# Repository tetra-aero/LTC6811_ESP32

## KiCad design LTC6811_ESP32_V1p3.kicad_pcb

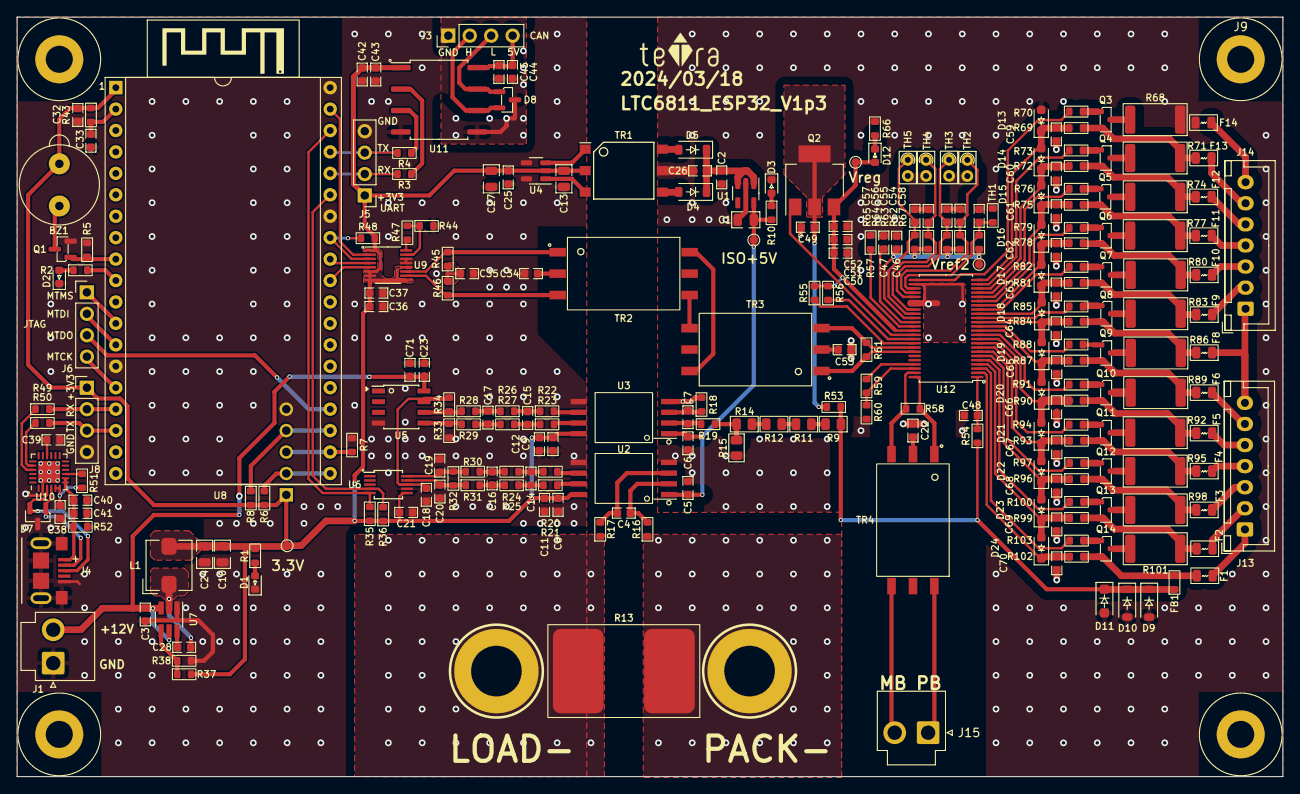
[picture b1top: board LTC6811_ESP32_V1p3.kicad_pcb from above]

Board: 2 copper layers, 150.0 x 90.0 mm, 262 parts (1 on the bottom side), 184 nets.

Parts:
BAT1: BAT-; Battery_6mm×10mm_Cell_half_2
BAT-1: BAT-; Battery_6mm×10mm_Cell_half_2
BZ1: AI-1027-TWT-5V; Beeper_AI-1027-TWT-5V
C1, C10, C13, C24, C27: 10uF/16V; C_0805_2012Metric
C2, C5, C6, C8, C9, C18, C19, C20, C21, C23, C25, C28, C32, C33, C37, C40, C43, C45, C48, C49, C54, C55, C56, C57, C58, C59, C60, C61, C62, C63, C64, C65, C66, C67, C68, C69, C70: 100nF/100V; C_0603_1608Metric
C3, C11, C12, C38, C41: 2.2uF/25V; C_0603_1608Metric
C4, C7: 330pF/100V; C_0603_1608Metric
C14, C15: 2.2nF/16V; C_0603_1608Metric
C16, C17: 220pF/50V; C_0603_1608Metric
C22, C53: 100pF/100V; C_0603_1608Metric
C26, C39: 4.7uF/16V; C_0603_1608Metric
C34, C35: 10nF/100V; C_0603_1608Metric
C36, C42, C44, C46, C47, C50, C51, C52, C71: 1uF/25V; C_0603_1608Metric
D1, D2, D3, D12: LED Red; LED_0603_1608Metric
D4, D5: MBR0520; D_SOD-123
D7, D8: ESD24VS2U; SOT-23
D9, D10: 1N4148W; D_SOD-123
D11: BZT52H-C62; D_SOD-123F
D13, D14, D15, D16, D17, D18, D19, D20, D21, D22, D23, D24: PDZ7.5B; D_SOD-323_HandSoldering
F1, F2, F3, F4, F5, F6, F8, F9, F10, F11, F12, F13, F14: MPZ2012S102ATD25; Fuse_0805_2012Metric
FB1: BLM18PG330SN1D; R_0603_1608Metric
J1, J15: PB MB; JST_VH_B2P-VH-B_1x02_P3.96mm_Vertical
J2: OLED /NC; PinHeader_1x05_P2.54mm_Vertical
J3: CAN /NC; PinHeader_1x04_P2.54mm_Vertical
J4: USB; Micro_USB_B-2013499-1
J5: UART /NC; PinHeader_1x04_P2.54mm_Vertical
J6: JTAG /NC; PinHeader_1x04_P2.54mm_Vertical
J8: SERIAL /NC; PinHeader_1x04_P2.54mm_Vertical
J9, J10, J11, J12: Hole /NC; MountingHole_3.2mm_M3_ISO7380_Pad
J13, J14: B7B-XH-A; JST_XH_B7B-XH-A_1x07_P2.50mm_Vertical_BAT_6S
L1: 3.3uH; L_Bourns_SRP5030T
LOGO1: teTra /NC; teTra-LOGO
Q1: BSS138; SOT-23
Q2: NSV1C201MZ4; SOT-223
Q3, Q4, Q5, Q6, Q7, Q8, Q9, Q10, Q11, Q12, Q13, Q14: TSM2323; SOT-23
R1, R2, R10: 470R; R_0603_1608Metric
R3, R4, R55, R57: 0; R_0603_1608Metric
R5: 1.5K; R_0603_1608Metric
R6, R7, R8, R35, R36: 4.7K; R_0603_1608Metric
R9, R11, R12, R14: 470KΩ ±0.1% 250mW; R_0805_2012Metric
R13: 0.1MR 1% 15W; R_PSR500HTQFB0L10_Metric_Pad5.2x8.75mm_HandSolder
R15: 1KΩ ±0.1% 250mW; R_0805_2012Metric
R16, R17, R18, R24, R25, R26, R27, R32: 1K; R_0603_1608Metric
R19: 10R; R_0603_1608Metric
R20, R21, R22, R23, R53, R54, R61, R69, R72, R75, R78, R81, R84, R87, R90, R93, R96, R99, R102: 100R; R_0603_1608Metric
R28, R29: 5.6K; R_0603_1608Metric
R30, R31, R70, R73, R76, R79, R82, R85, R88, R91, R94, R97, R100, R103: 3.3K; R_0603_1608Metric
R33, R34: 33K; R_0603_1608Metric
R37, R58, R62, R63, R64, R65, R67: 100K; R_0603_1608Metric
R38: 22.1K; R_0603_1608Metric
R43, R51, R52: 10K; R_0603_1608Metric
R44, R60: 806R; R_0603_1608Metric
R45, R46: 51R; R_0603_1608Metric
R47, R59, R66: 1.2K; R_0603_1608Metric
R48: 2K; R_0603_1608Metric
R49, R50: 240R; R_0603_1608Metric
R56: 1M; R_0603_1608Metric
R68, R71, R74, R77, R80, R83, R86, R89, R92, R95, R98, R101: 36R 1W 2512; R_2512_6332Metric
TH1: 100K NTC; R_0603_1608Metric
TH2, TH3, TH4, TH5: 100K NTC; R_Axial_DIN0204_L3.6mm_D1.6mm_P1.90mm_Vertical
TP1, TP2, TP3, TP4: TestPoint; TestPoint_Pad_D1.0mm
TR1: Transformer; WURTH-760390015
TR2, TR3, TR4: HM2108NL
U1: TPS76350; SOT-23-5
U2: AMC1301 or AMC1302; SSO-8_6.8x5.9mm_P1.27mm_Clearance8mm
U3: AMC1301; SSO-8_6.8x5.9mm_P1.27mm_Clearance8mm
U4: SN6501DBV; SOT-23-5
U5: OPA2197IDR; SOIC-8_3.9x4.9mm_Pitch1.27mm
U6: ISL28022; MSOP-10_3x3mm_P0.5mm
U7: LMR51420XDDCR; SOT-23-6_Handsoldering
U8: ESP32-DevKitC V4; ESP32-DevKitc V4_DIP-38_27.9mm×48.2mm
U9: LTC6820; MSOP-16_3x4mm_P0.5mm
U10: CP2104; HVQFN-24-1EP_4x4mm_P0.5mm_EP2.6x2.6mm
U11: ISO1050DUBR; SOP-8_6.62x9.15mm_P2.54mm
U12: LTC6811HG-1; TSSOP-48_6.1x12.5mm_P0.5mm

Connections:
+3V3: BZ1.1 (-), C8.1, C9.1, C10.1, C11.1, C12.1, C13.1, C21.2, C24.1, C25.1, C27.1, C32.2, C36.2, C37.1, C42.1, C43.1, J2.1, J5.1, J8.1, L1.2, R1.2, R6.2, R8.2, R35.1, R36.1, R37.2, R43.1, R48.1, TP2.1, TR1.2, U2.8 (VDD2), U3.8 (VDD2), U4.2 (VCC), U6.6 (Vs), U8.1 (3V3), U9.1 (EN), U9.6 (Vcc0), U9.7 (POL), U9.8 (PHA), U9.9 (VCC), U9.12 (MSTR), U11.1 (Vcc1)
+12V: C3.1, C23.1, C71.2, J1.2, U5.8 (V+), U7.3 (VIN), U7.5 (EN)
/BAT+: D9.1 (K), D10.1 (K), D11.1 (K), FB1.1, R9.1, R53.1, R54.1
/CAN/5V_CAN: C44.1, C45.2, J3.4, U11.8 (Vcc2)
/CAN/CANH: D8.2 (K), J3.2, U11.6 (CANL)
/CAN/CANL: D8.1 (K), J3.3, U11.7 (CANH)
/CAN/CAN_GND: C44.2, C45.1, D8.3 (A), J3.1, U11.5 (GND2)
/CAN/CAN_RX: R3.2, U11.2 (RXD)
/CAN/CAN_TX: R4.2, U11.3 (TXD)
/LTC6811/C1: F13.1, J14.1 (Pin_2)
/LTC6811/C1_G: F14.1, J14.0 (Pin_1)
/LTC6811/C2: F12.1, J14.2 (Pin_3)
/LTC6811/C3: F11.1, J14.3 (Pin_4)
/LTC6811/C4: F10.1, J14.4 (Pin_5)
/LTC6811/C5: F9.1, J14.5 (Pin_6)
/LTC6811/C6: F8.1, J13.0 (Pin_1), J14.6 (Pin_7)
/LTC6811/C7: F6.1, J13.1 (Pin_2)
/LTC6811/C8: F5.1, J13.2 (Pin_3)
/LTC6811/C9: F4.1, J13.3 (Pin_4)
/LTC6811/C10: F3.1, J13.4 (Pin_5)
/LTC6811/C11: F2.1, J13.5 (Pin_6)
/LTC6811/C12: F1.1, J13.6 (Pin_7)
/LTC6811/DRIVE: Q2.1 (B), U12.38 (DRIVE)
/LTC6811/IMA: R61.2, TR3.3, U12.41 (IMA)
/LTC6811/IMB: R58.1, TR4.3, U12.47 (IMB)
/LTC6811/IPA: R61.1, TR3.1, U12.42 (IPA)
/LTC6811/IPB: R58.2, TR4.1, U12.48 (IPB)
/LTC6811/T1: C58.1, R67.2, TH1.1, U12.27 (GPIO1)
/LTC6811/T2: C54.1, R62.1, TH2.1, U12.28 (GPIO2)
/LTC6811/T3: C55.1, R63.1, TH3.1, U12.29 (GPIO3)
/LTC6811/T4: C56.1, R64.1, TH4.1, U12.32 (GPIO4)
/LTC6811/T5: C57.1, R65.1, TH5.1, U12.33 (GPIO5)
/LTC6811/Vref2: C46.1, R62.2, R63.2, R64.2, R65.2, R67.1, TP4.1, U12.34 (Vref2)
/LTC6811/Vreg: C50.1, C51.1, C52.1, D12.2 (A), Q2.3 (E), R55.2, R56.2, TP3.1, U12.37 (Vreg)
/LTC6811/cell1/C: C59.1, D13.1 (K), D14.2 (A), R69.1, U12.24 (C1)
/LTC6811/cell1/C+: F13.2, Q3.2 (S), R69.2, R71.1
/LTC6811/cell1/S: R70.1, U12.25 (S1)
/LTC6811/cell2/C: C60.1, D14.1 (K), D15.2 (A), R72.1, U12.22 (C2)
/LTC6811/cell2/C+: F12.2, Q4.2 (S), R72.2, R74.1
/LTC6811/cell2/S: R73.1, U12.23 (S2)
/LTC6811/cell3/C: C61.1, D15.1 (K), D16.2 (A), R75.1, U12.20 (C3)
/LTC6811/cell3/C+: F11.2, Q5.2 (S), R75.2, R77.1
/LTC6811/cell3/S: R76.1, U12.21 (S3)
/LTC6811/cell4/C: C62.1, D16.1 (K), D17.2 (A), R78.1, U12.18 (C4)
/LTC6811/cell4/C+: F10.2, Q6.2 (S), R78.2, R80.1
/LTC6811/cell4/S: R79.1, U12.19 (S4)
/LTC6811/cell5/C: C63.1, D17.1 (K), D18.2 (A), R81.1, U12.16 (C5)
/LTC6811/cell5/C+: F9.2, Q7.2 (S), R81.2, R83.1
/LTC6811/cell5/S: R82.1, U12.17 (S5)
/LTC6811/cell6/C: C64.1, D18.1 (K), D19.2 (A), R84.1, U12.14 (C6)
/LTC6811/cell6/C+: F8.2, Q8.2 (S), R84.2, R86.1
/LTC6811/cell6/S: R85.1, U12.15 (S6)
/LTC6811/cell7/C: C65.1, D19.1 (K), D20.2 (A), R87.1, U12.12 (C7)
/LTC6811/cell7/C+: F6.2, Q9.2 (S), R87.2, R89.1
/LTC6811/cell7/S: R88.1, U12.13 (S7)
/LTC6811/cell8/C: C66.1, D20.1 (K), D21.2 (A), R90.1, U12.10 (C8)
/LTC6811/cell8/C+: F5.2, Q10.2 (S), R90.2, R92.1
/LTC6811/cell8/S: R91.1, U12.11 (S8)
/LTC6811/cell9/S: R94.1, U12.9 (S9)
/LTC6811/cell10/C: C68.1, D22.1 (K), D23.2 (A), R96.1, U12.6 (C10)
/LTC6811/cell10/C+: F3.2, Q12.2 (S), R96.2, R98.1
/LTC6811/cell10/C-: F4.2, Q11.2 (S), R93.2, R95.1
/LTC6811/cell10/CM: C67.1, D21.1 (K), D22.2 (A), R93.1, U12.8 (C9)
/LTC6811/cell10/S: R97.1, U12.7 (S10)
/LTC6811/cell11/C: C69.1, D23.1 (K), D24.2 (A), R99.1, U12.4 (C11)
/LTC6811/cell11/C+: F2.2, Q13.2 (S), R99.2, R101.1
/LTC6811/cell11/S: R100.1, U12.5 (S11)
/LTC6811/cell12/C: C70.1, D24.1 (K), R102.1, U12.2 (C12)
/LTC6811/cell12/C+: F1.2, FB1.2, Q14.2 (S), R102.2
/LTC6811/cell12/S: R103.1, U12.3 (S12)
/MA: TR2.6, TR3.6
/MCU/BUZZER: Q1.1 (G), R5.2, U8.9 (IO25)
/MCU/CAN_RX: J5.2, R3.1, U8.34 (RXD0)
/MCU/CAN_TX: J5.3, R4.1, U8.35 (TXD0)
/MCU/IM: R46.1, TR2.3, U9.10 (IM)
/MCU/IP: R45.2, TR2.1, U9.11 (IP)
/MCU/LED0: R2.2, U8.10 (IO26)
/MCU/MISO: R48.2, U8.31 (IO19), U9.3 (MISO)
/MCU/MOSI: U8.37 (IO23), U9.2 (MOSI)
/MCU/MTCK: J6.4, U8.15 (IO13)
/MCU/MTDI: J6.2, U8.13 (IO12)
/MCU/MTDO: J6.3, U8.23 (IO15)
/MCU/MTMS: J6.1, U8.12 (IO14)
/MCU/NRST: C33.2, R43.2, U8.2 (EN)
/MCU/OLED_RST: J2.2, R6.1, U8.20 (CLK)
/MCU/OLED_SCL: J2.4, R8.1, U8.22 (SD1)
/MCU/OLED_SDA: J2.3, R7.2, U8.21 (SD0)
/MCU/RX_USB: J8.2, R49.2, U8.16 (SD2)
/MCU/SCK: U8.30 (IO18), U9.4 (SCK)
/MCU/SCL: R35.2, U6.5 (SCL), U8.36 (IO22)
/MCU/SDA: R36.2, U6.4 (SDA), U8.33 (IO21)
/MCU/SS: U8.29 (IO5), U9.5 (CSB)
/MCU/TX_USB: J8.3, R50.2, U8.17 (SD3)
/PA: TR2.4, TR3.4
/PowerMonitor/BAT-: BAT-1.1, R13.2, R17.1
/PowerMonitor/ISO+5V: C1.1, C5.1, C6.1, R10.2, TP1.1, U1.5 (VOUT), U2.1 (VDD1), U3.1 (VDD1)
/PowerMonitor/VBAT_SENSE: C18.2, R34.2, U5.7, U6.8 (Vbus)
/USB/D+: D7.2 (K), J4.3 (D+), U10.3 (D+)
/USB/D-: D7.1 (K), J4.2 (D-), U10.4 (D-)
/USB/Vusb: C40.1, C41.1, J4.1 (VBUS), R52.1, U10.7 (REGIN), U10.8 (VBUS)
GND: C3.2, C8.2, C9.2, C10.2, C11.2, C12.2, C13.2, C18.1, C19.1, C20.1, C21.1, C23.2, C24.2, C25.2, C27.2, C32.1, C33.1, C34.2, C35.1, C36.1, C37.2, C38.2, C39.2, C40.2, C41.2, C42.2, C43.2, C71.1, D1.1 (K), D2.1 (K), D7.3 (A), J1.1, J2.5, J4.5 (GND), J4.6 (Shield), J5.4, J8.4, Q1.2 (S), R5.1, R7.1, R33.2, R38.2, R44.2, R52.2, U2.5 (GND2), U3.5 (GND2), U4.4 (GND), U4.5 (GND), U5.4 (V-), U6.7 (GND), U7.1 (GND), U8.14 (GND), U8.32 (GND), U8.38 (GND), U9.13 (SLOW), U9.14 (GND), U10.2 (GND), U10.25 (PAD), U11.4 (GND1)
GND_PACK: BAT1.1, C1.2, C2.2, C5.2, C6.2, C22.2, C26.2, C46.2, C47.2, C48.2, C49.2, C50.2, C51.2, C52.2, C53.2, C54.2, C55.2, C56.2, C57.2, C58.2, C59.2, C60.2, C61.2, C62.2, C63.2, C64.2, C65.2, C66.2, C67.2, C68.2, C69.2, C70.2, D3.1 (K), D9.2 (A), D10.2 (A), D11.2 (A), D13.2 (A), F14.2, R13.1, R15.2, R16.1, R18.2, R57.2, R60.2, R66.2, R68.1, TH1.2, TH2.2, TH3.2, TH4.2, TH5.2, TR1.5, U1.2 (GND), U2.4 (GND1), U3.4 (GND1), U12.26 (C0), U12.30 (V-**), U12.31 (V-)
unnamed: BZ1.2 (+), Q1.3 (D)
unnamed: C14.1, R20.1, R24.1
unnamed: C14.2, R21.1, R25.1
unnamed: C15.1, R22.1, R26.1
unnamed: C15.2, R23.1, R27.1
unnamed: C16.1, R24.2, R30.2
unnamed: C16.2, R25.2, R31.2
unnamed: C17.1, R26.2, R28.1
unnamed: C17.2, R27.2, R29.1
unnamed: C22.1, TR4.2
unnamed: C34.1, TR2.2
unnamed: C35.2, R45.1, R46.2
unnamed: C49.1, Q2.2 (C), Q2.4 (C), R53.2
unnamed: C53.1, TR3.2
unnamed: D1.2 (A), R1.1
unnamed: D2.2 (A), R2.1
unnamed: D3.2 (A), R10.1
unnamed: D4.2 (A), TR1.4
unnamed: C2.1, C26.1, D4.1 (K), D5.1 (K), U1.1 (VIN), U1.3 (EN)
unnamed: D5.2 (A), TR1.6
unnamed: D12.1 (K), R66.1
unnamed: J15.1, TR4.4
unnamed: J15.2, TR4.6
unnamed: Q3.3 (D), R68.2
unnamed: Q3.1 (G), R70.2
unnamed: Q4.3 (D), R71.2
unnamed: Q4.1 (G), R73.2
unnamed: Q5.3 (D), R74.2
unnamed: Q5.1 (G), R76.2
unnamed: Q6.3 (D), R77.2
unnamed: Q6.1 (G), R79.2
unnamed: Q7.3 (D), R80.2
unnamed: Q7.1 (G), R82.2
unnamed: Q8.3 (D), R83.2
unnamed: Q8.1 (G), R85.2
unnamed: Q9.3 (D), R86.2
unnamed: Q9.1 (G), R88.2
unnamed: Q10.3 (D), R89.2
unnamed: Q10.1 (G), R91.2
unnamed: Q11.3 (D), R92.2
unnamed: Q11.1 (G), R94.2
unnamed: Q12.3 (D), R95.2
unnamed: Q12.1 (G), R97.2
unnamed: Q13.3 (D), R98.2
unnamed: Q13.1 (G), R100.2
unnamed: Q14.3 (D), R101.2
unnamed: Q14.1 (G), R103.2
unnamed: R9.2, R11.1
unnamed: R11.2, R12.1
unnamed: R12.2, R14.1
unnamed: R14.2, R15.1, R19.1
unnamed: C4.2, R17.2, U2.3 (VINN)
unnamed: C4.1, R16.2, U2.2 (VINP)
unnamed: R20.2, U2.6 (VOUTN)
unnamed: R21.2, U2.7 (VOUTP)
unnamed: C7.2, R18.1, U3.3 (VINN)
unnamed: C7.1, R19.2, U3.2 (VINP)
unnamed: R22.2, U3.6 (VOUTN)
unnamed: R23.2, U3.7 (VOUTP)
unnamed: TR1.3, U4.1 (D1)
unnamed: TR1.1, U4.3 (D2)
unnamed: R29.2, R33.1, U5.5 (+)
unnamed: R28.2, R34.1, U5.6 (-)
unnamed: C19.2, R30.1, R32.1, U6.10 (Vin+)
unnamed: C20.2, R31.1, R32.2, U6.9 (Vin-)
unnamed: C28.2, U7.6 (CB)
unnamed: R37.1, R38.1, U7.4 (FB)
unnamed: C28.1, L1.1, U7.2 (SW)
unnamed: R47.1, U9.16 (IBIAS)
unnamed: R44.1, R47.2, U9.15 (ICMP)
unnamed: R50.1, U10.20 (RXD)
unnamed: R49.1, U10.21 (TXD)
unnamed: C39.1, U10.16 (VPP)
unnamed: R51.2, U10.9 (~RST)
unnamed: R57.1, U12.36 (DTEN)
unnamed: R59.1, U12.45 (IBIAS)
unnamed: R59.2, R60.1, U12.46 (ICMP)
unnamed: R55.1, U12.40 (ISOMD)
unnamed: C48.1, R54.2, U12.1 (V+)
unnamed: C47.1, U12.35 (Vref1)
unnamed: R56.1, U12.39 (WDT)
VDD: C38.1, R51.1, U10.5 (VIO), U10.6 (VDD)

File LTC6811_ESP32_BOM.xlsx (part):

LTC6811_ESP32_BOM
NO. | Reference | Value | Footprint | Datasheet | Description | Link | MPN | Quantity
1 | BZ1 | AI-1027-TWT-5V | ENNOID:BUZZER | https://www.puiaudio.com/media/SpecSheet/AI-1027-TWT-5V-2-R.pdf | Buzzers Indicator, Internally Driven Electromechanical/Magnetic 5 V 30mA 2.73kH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 | https://www.digikey.jp/en/products/detail/pui-audio-inc/AI-1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 | AI-1027-TWT-5V-2-R | 1
2 | C1, C3, C13 | 10uF 25V | Capacitor_SMD:C_0805_2012Metric | https://mm.digikey.com/Volume0/opasdata/d220001/medias/docus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 | 10 uF ±10% 25V Ceramic Capacitor X5R 0805 (2012 Metric) | https://www.digikey.jp/en/products/detail/samsung-electro-me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 | CL21A106KAYNNNE | 3
3 | C2, C5, C6, C8-C10, C18-C21, C26, C28, C37, C40, C43, C48, C49, C54-C70 | 100nF 100V | Capacitor_SMD:C_0603_1608Metric | https://www.digikey.jp/en/products/detail/samsung-electro-me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 | 0.1 uF ±10% 100V Ceramic Capacitor X7R 0603 (1608 Metric) | https://www.digikey.jp/en/products/detail/samsung-electro-me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 | CL10B104KC8NNNC | 34
4 | C4, C7 | 330pF 100V | Capacitor_SMD:C_0603_1608Metric | https://www.yageo.com/upload/media/product/productsearch/dat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 | 330 pF ±10% 100V Ceramic Capacitor X7R 0603 (1608 Metric) | https://www.digikey.jp/en/products/detail/murata-electronics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 | CC0603KRX7R0BB331 | 2
5 | C11, C12, C38, C39, C41 | 2.2uF 16V | Capacitor_SMD:C_0603_1608Metric | https://connect.kemet.com:7667/gateway/IntelliData-Component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 | 2.2 uF ±10% 16V Ceramic Capacitor X5R 0603 (1608 Metric) | https://www.digikey.jp/en/products/detail/kemet/C0603C225K4P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 | C0603C225K4PAC7867 | 5
6 | C14, C15 | 2.2nF 16V | Capacitor_SMD:C_0603_1608Metric | https://connect.kemet.com:7667/gateway/IntelliData-Component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 | 2200 pF ±10% 16V Ceramic Capacitor X7R 0603 (1608 Metric) | https://www.digikey.jp/en/products/detail/kemet/C0603C222K4R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 | C0603C222K4RECAUTO | 2
7 | C16, C17 | 220pF 50V | Capacitor_SMD:C_0603_1608Metric | https://connect.kemet.com:7667/gateway/IntelliData-Component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 | 220 pF ±1% 50V Ceramic Capacitor C0G, NP0 0603 (1608 Metric) | https://www.digikey.jp/en/products/detail/kemet/C0603C221F5G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 | C0603C221F5GAC7867 | 2
8 | C24, C25 | 2.2uF 100V | Capacitor_SMD:C_1206_3216Metric | https://www.samsungsem.com/resources/file/global/support/pro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 | 2.2 uF ±10% 100V Ceramic Capacitor X7R 1206 (3216 Metric) | https://www.digikey.jp/en/products/detail/samsung-electro-me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 | CL31B225KCHSNNE | 2
9 | C27, C34, C35 | 10nF 100V | Capacitor_SMD:C_0603_1608Metric | https://search.murata.co.jp/Ceramy/image/img/A01X/G101/ENG/G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 | 10000 pF ±10% 100V Ceramic Capacitor X7R 0603 (1608 Metric) | https://www.digikey.jp/en/products/detail/murata-electronics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 | GCM188R72A103KA37D | 3
10 | C29 | 6.8pF 50V | Capacitor_SMD:C_0603_1608Metric | https://datasheets.kyocera-avx.com/C0GNP0-KGM.pdf | 6.8 pF ±0.5pF 50V Ceramic Capacitor C0G, NP0 0603 (1608 Metric) | https://www.digikey.jp/en/products/detail/kyocera-avx/KGM15A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 | KGM15ACG1H6R8DT | 1
11 | C30 | 3nF 16V | Capacitor_SMD:C_0603_1608Metric | https://connect.kemet.com:7667/gateway/IntelliData-Component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 | 3000 pF ±10% 16V Ceramic Capacitor X8R 0603 (1608 Metric) | https://www.digikey.jp/en/products/detail/kemet/C0603C302K4H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 | C0603C302K4HACAUTO | 1
12 | C31 | 47uF 16V | Capacitor_SMD:CP_Elec_5x4.4 | https://industrial.panasonic.com/cdbs/www-data/pdf/AAB8000/A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 | 47 uF 16 V Aluminum - Polymer Capacitors Radial, Can - SMD 25mOhm 5000 Hrs @ 10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 | https://www.digikey.jp/en/products/detail/panasonic-electron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 | 16SVPG47M | 1
13 | C32, C33, C45 | 100nF 50V | Capacitor_SMD:C_0603_1608Metric | https://mm.digikey.com/Volume0/opasdata/d220001/medias/docus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 | 0.1 µF ±10% 50V Ceramic Capacitor X7R 0603 (1608 Metric) | https://www.digikey.jp/en/products/detail/samsung-electro-me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 | CL10B104KB8NNNC | 3
14 | C36, C42, C44, C46, C47, C50-C52 | 1uF 25V | Capacitor_SMD:C_0603_1608Metric | https://mm.digikey.com/Volume0/opasdata/d220001/medias/docus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 | 1 µF ±10% 25V Ceramic Capacitor X5R 0603 (1608 Metric) | https://www.digikey.jp/en/products/detail/samsung-electro-me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 | CL10A105KA8NNNC | 8
15 | C22,C53 | 100pF 100V | Capacitor_SMD:C_0603_1608Metric | https://search.murata.co.jp/Ceramy/image/img/A01X/G101/ENG/G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 | 100 pF ±5% 100V Ceramic Capacitor C0G, NP0 0603 (1608 Metric) | https://www.digikey.jp/en/products/detail/murata-electronics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 | GCM1885C2A101JA16D | 2
16 | D1-D3, D12 | LED Red | LED_SMD:LED_0603_1608Metric | https://optoelectronics.liteon.com/upload/download/DS-22-99-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 | Red 631nm LED Indication - Discrete 2V 0603 (1608 Metric) | https://www.digikey.jp/en/products/detail/liteon/LTST-C190KR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 | LTST-C190KRKT | 4
17 | D4, D5 | MBR0520 | Diode_SMD:D_SOD-123 | http://www.mccsemi.com/up_pdf/MBR0520~MBR0580(SOD123).pdf | Diode 20 V 500mA Surface Mount SOD-123 | https://www.digikey.jp/en/products/detail/micro-commercial-c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 | MBR0520-TP | 2
18 | D6 | P6SMB22A | Diode_SMD:D_SMB | https://mm.digikey.com/Volume0/opasdata/d220001/medias/docus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 | 30.6V Clamp 19.9A Ipp Tvs Diode Surface Mount SMB (DO-214AA) | https://www.digikey.jp/en/products/detail/bourns-inc/P6SMB22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 | P6SMB22A | 1
19 | D7, D8 | ESD24VS2U | Package_TO_SOT_SMD:SOT-23 | https://www.infineon.com/dgdl/Infineon-ESD24VS2U-DS-v01_01-e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 | 41V Clamp 5A (8/20us) Ipp Tvs Diode Surface Mount PG-SOT23 | https://www.digikey.jp/en/products/detail/infineon-technolog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 | ESD24VS2UE6327HTSA1 | 2
20 | D9, D10 | 1N4148W | Diode_SMD:D_SOD-123 | https://www.diodes.com/assets/Datasheets/BAV16W_1N4148W.pdf | Diode 100 V 300mA Surface Mount SOD-123 | https://www.digikey.jp/en/products/detail/diodes-incorporate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 | 1N4148W-7-F | 2
21 | D11 | BZT52H-C62 | Diode_SMD:D_SOD-123F | https://assets.nexperia.com/documents/data-sheet/BZT52H_SER.pdf | Zener Diode 62 V 375 mW ±5% Surface Mount SOD-123F | https://www.digikey.jp/en/products/detail/nexperia-usa-inc/B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 | BZT52H-C62,115 | 1
22 | D13-D24 | PDZ7.5B | Diode_SMD:D_SOD-323 | https://assets.nexperia.com/documents/data-sheet/PDZ-B_SER.pdf | Zener Diode 7.6 V 400 mW ±2% Surface Mount SOD-323 | https://www.digikey.jp/en/products/detail/nexperia-usa-inc/P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 | PDZ7.5BZ | 12
23 | F1-F14 | MPZ2012S102ATD25 | Fuse:Fuse_0805_2012Metric | https://product.tdk.com/en/system/files?file=dam/doc/product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 | 1 kOhms @ 100 MHz 1 Power Line Ferrite Bead 0805 (2012 Metric) 1.5A 150mOhm | https://www.digikey.jp/en/products/detail/tdk-corporation/MP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 | MPZ2012S102ATD25 | 14
24 | FB1 | BLM18PG330SN1D | Resistor_SMD:R_0603_1608Metric | https://www.murata.com/en-us/products/productdata/8796738650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 | 33 Ohms @ 100 MHz 1 Power Line Ferrite Bead 0603 (1608 Metric) 3A 25mOhm | https://www.digikey.jp/en/products/detail/murata-electronics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 | BLM18PG330SN1D | 1
25 | J2 | OLED /NC | Connector_PinHeader_2.54mm:PinHeader_1x05_P2.54mm_Vertical | https://tools.molex.com/pdm_docs/sd/705430001_sd.pdf | Connector Header Through Hole 5 position 0.100" (2.54mm) | https://www.digikey.jp/en/products/detail/molex/0705430004/1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 | 70543-0004 | 1
26 | J3 | CAN /NC | Connector_PinHeader_2.54mm:PinHeader_1x04_P2.54mm_Vertical | https://suddendocs.samtec.com/prints/tsw-xxx-xx-x-x-xx-xxx-f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 | Connector Header Through Hole 4 position 0.100" (2.54mm) | https://www.digikey.jp/en/products/detail/samtec-inc/TSW-104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 | TSW-104-07-G-S | 1
27 | J4 | USB | Connector_USB:Micro_USB_B-2013499-1 | https://www.te.com/usa-en/product-2013499-1.datasheet.pdf | USB - micro B USB 2.0 Receptacle Connector 5 Position Surface Mount, Right Angl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 | https://www.digikey.jp/en/products/detail/te-connectivity-am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 | 2013499-1 | 1
28 | J5 | UART /NC | Connector_PinHeader_2.54mm:PinHeader_1x04_P2.54mm_Vertical | https://suddendocs.samtec.com/prints/tsw-xxx-xx-x-x-xx-xxx-f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 | Connector Header Through Hole 4 position 0.100" (2.54mm) | https://www.digikey.jp/en/products/detail/samtec-inc/TSW-104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 | TSW-104-07-G-S | 0
29 | J6 | JTAG /NC | Connector_PinHeader_2.54mm:PinHeader_1x04_P2.54mm_Vertical | https://suddendocs.samtec.com/prints/tsw-xxx-xx-x-x-xx-xxx-f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 | Connector Header Through Hole 4 position 0.100" (2.54mm) | https://www.digikey.jp/en/products/detail/samtec-inc/TSW-104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 | TSW-104-07-G-S | 0
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
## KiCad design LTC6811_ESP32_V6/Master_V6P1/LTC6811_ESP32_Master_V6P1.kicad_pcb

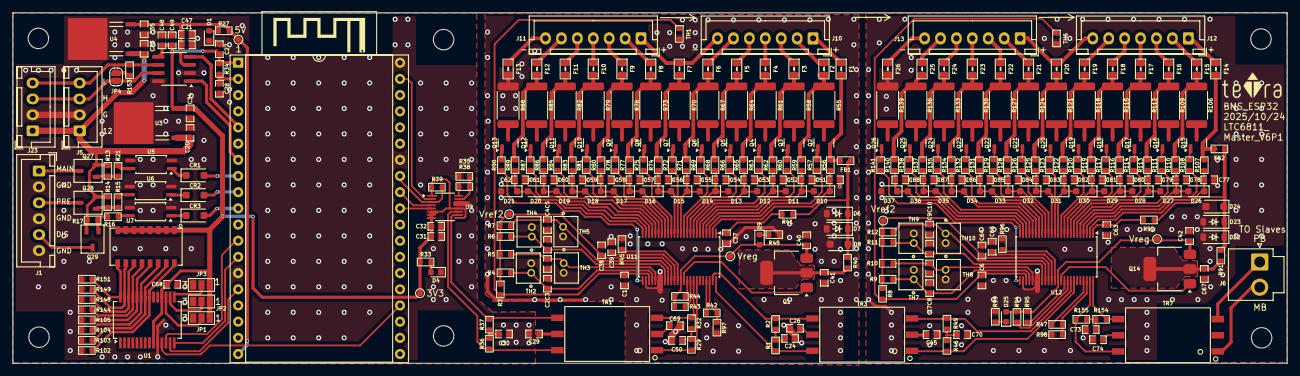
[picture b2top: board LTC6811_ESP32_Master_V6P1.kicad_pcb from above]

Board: 2 copper layers, 200.0 x 55.0 mm, 341 parts (1 on the bottom side), 253 nets.

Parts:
C1, C2, C3, C4, C5, C6, C7, C8, C9, C10, C27, C28, C32, C37, C41, C47, C49, C51, C52, C53, C54, C55, C56, C57, C58, C59, C60, C61, C62, C63, C67, C68, C77, C78, C79, C80, C81, C82, C83, C84, C85, C86, C87, C88: 100nF/100V; C_0603_1608Metric
C20, C33: 2.2uF/25V; C_0603_1608Metric
C21, C48: 1nF/16V; C_0603_1608Metric
C24, C26, C29, C30, C45, C50, C69, C70, C73, C74: 10nF/100V; C_0603_1608Metric
C31, C34, C35, C38, C39, C64, C65: 1uF/25V; C_0603_1608Metric
C40, C42: 4.7uF/16V; C_0603_1608Metric
CR1, CR2, CR3: S-562T; D_SOD-123F
D1, D4, D9, D25: LED Red; LED_0603_1608Metric
D6, D7, D22, D23: 1N4148W; D_SOD-123
D8, D24: BZT52H-C62; D_SOD-123F
D10, D11, D12, D13, D14, D15, D16, D17, D18, D19, D20, D21, D26, D27, D28, D29, D30, D31, D32, D33, D34, D35, D36, D37: PDZ7.5B; D_SOD-323_HandSoldering
F1, F2, F3, F4, F5, F6, F7, F8, F9, F10, F11, F12, F13, F14, F15, F16, F17, F18, F19, F20, F21, F22, F23, F24, F25, F26: MPZ2012S102ATD25; Fuse_0805_2012Metric
FB1, FB2: BLM18PG330SN1D; R_0603_1608Metric
J1: B6P-XH; JST_XH_B6B-XH-A_1x06_P2.50mm_Vertical
J3, J4, J7, J18, J19, J21: Hole /NC; MountingHole_3.2mm_M3_ISO7380
J5, J23: CAN; JST_XH_B4B-XH-A_1x04_P2.50mm_Vertical
J6: B2P-VH-B; JST_VH_B2P-VH-B_1x02_P3.96mm_Vertical
J10, J11, J12, J13: B7B-XH-A; JST_XH_B7B-XH-A_1x07_P2.50mm_Vertical_BAT_6S
JP1, JP2, JP3: SolderJumper_3_Bridged12; SolderJumper-3_P1.3mm_Open_Pad1.0x1.5mm_NumberLabels
JP4: SolderJumper_2_Open; SolderJumper-2_P1.3mm_Open_RoundedPad1.0x1.5mm
LOGO1, LOGO2: teTra /NC; teTra-LOGO
Q1, Q14: NSV1C201MZ4; SOT-223
Q2, Q3, Q4, Q5, Q6, Q7, Q8, Q9, Q10, Q11, Q12, Q13, Q15, Q16, Q17, Q18, Q19, Q20, Q21, Q22, Q23, Q24, Q25, Q26: TSM2323; SOT-23
Q27, Q28, Q29: SSM3J332R,LF; TSOT-23
R1, R2, R36, R37, R46, R49: 49.9R; R_0603_1608Metric
R3, R4, R5, R6, R7, R8, R9, R10, R11, R12, R13, R14, R16, R34, R102, R103, R104, R105, R144, R148, R149, R151: 10K; R_0603_1608Metric
R15, R17, R21, R35, R38, R42, R47, R97, R98: 1K; R_0603_1608Metric
R27, R33: 470R; R_0603_1608Metric
R29, R32, R154, R155: 51R; R_0603_1608Metric
R39: 2K; R_0603_1608Metric
R40, R41, R56, R59, R62, R65, R68, R71, R74, R77, R80, R83, R86, R89, R91, R92, R107, R110, R113, R116, R119, R122, R125, R128, R131, R134, R137, R140: 100R; R_0603_1608Metric
R43, R45, R94, R96: 0; R_0603_1608Metric
R44, R95: 1M; R_0603_1608Metric
R48, R99: 1.2K; R_0603_1608Metric
R55, R58, R61, R64, R67, R70, R73, R76, R79, R82, R85, R88, R106, R109, R112, R115, R118, R121, R124, R127, R130, R133, R136, R139: 36R 1W 2512; R_2512_6332Metric
R57, R60, R63, R66, R69, R72, R75, R78, R81, R84, R87, R90, R108, R111, R114, R117, R120, R123, R126, R129, R132, R135, R138, R141: 3.3K; R_0603_1608Metric
R153: 120R; R_0603_1608Metric
SW1: 218-8LPSTJ; SW_218-8LPSTJ_11.33×6.05_P1.27
TH1, TH6: 10K NTC SMD; R_0603_1608Metric
TH2, TH3, TH4, TH5, TH7, TH8, TH9, TH10: 10K NTC; JST_ZR_B2B-ZR_1x02_P1.50mm_Vertical
TP1: 5V; TestPoint_Pad_D1.0mm
TP2: 3V3; TestPoint_Pad_D1.0mm
TP3, TP5: Vreg; TestPoint_Pad_D1.0mm
TP4, TP6: Vref2; TestPoint_Pad_D1.0mm
TR1, TR3, TR7: HM2108NL
U1: MCP23017T-E/SS; SSOP-28_5.3x10.2mm_P0.65mm
U2: MCP2562T-E/SN; SOIC-8_3.9x4.9mm_P1.27mm
U3: BD33FC0FP-E2; TO252-3_ROM
U4: BD50FC0FP-E2; TO252-3_ROM
U5, U6, U7: TLP291; SOIC-4_4.55x2.6mm_P1.27mm
U8: ESP32-DevKitC V4; ESP32-DevKitc V4_DIP-38_27.9mm×48.2mm
U9: LTC6820; MSOP-16_3x4mm_P0.5mm
U11, U12: LTC6811HG-1; TSSOP-48_6.1x12.5mm_P0.5mm

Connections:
+3V3: C27.2, C31.2, C32.1, C34.2, C48.1, C49.1, C68.2, JP1.1 (A), JP2.1 (A), JP3.1 (A), R33.2, R34.1, R39.1, SW1.1, SW1.2, SW1.3, SW1.4, SW1.5, SW1.6, SW1.7, SW1.8, TP2.1, U1.9 (VDD), U1.18 (~RESET), U2.5 (Vio), U3.3 (Vo), U8.1 (3V3), U9.1 (EN), U9.6 (Vcc0), U9.7 (POL), U9.8 (PHA), U9.9 (VCC), U9.12 (MSTR)
+5V: C21.1, C35.2, C47.1, R27.2, TP1.1, U2.3 (VDD), U4.3 (Vo), U8.19 (5V)
+12V: C20.1, C33.1, J5.1, J23.1, Q27.2 (S), Q28.2 (S), Q29.2 (S), R13.2, R14.2, R16.2, U3.1 (Vcc), U4.1 (Vcc)
/CAN/CAN_H: J5.3, J23.3, JP4.1 (A), U2.7 (CANH)
/CAN/CAN_L: J5.4, J23.4, R153.1, U2.6 (CANL)
/CAN/RXD: U2.4 (RXD), U8.5 (IO34)
/CAN/TXD: U2.1 (TXD), U8.7 (IO32)
/MCU/Discharge_Relay: J1.5, Q29.3 (D)
/MCU/Discharge_Relay_Control: CR3.2, U8.10 (IO26)
/MCU/HSPI_CS: U1.11 (~CS), U8.23 (IO15)
/MCU/HSPI_MISO: U1.14 (SO), U8.13 (IO12)
/MCU/HSPI_MOSI: U1.13 (SI), U8.15 (IO13)
/MCU/HSPI_SCK: U1.12 (SCK), U8.12 (IO14)
/MCU/IM: R37.1, TR1.4, U9.10 (IM)
/MCU/IP: R36.2, TR1.6, U9.11 (IP)
/MCU/Main_Relay: J1.1, Q27.3 (D)
/MCU/Main_Relay_Control: CR1.2, U8.8 (IO33)
/MCU/NRST: C28.2, R34.2, U8.2 (EN)
/MCU/Precharge_Relay: J1.3, Q28.3 (D)
/MCU/Precharge_Relay_Control: CR2.2, U8.9 (IO25)
/MCU/VSPI_CS: U8.29 (IO5), U9.5 (CSB)
/MCU/VSPI_MISO: R39.2, U8.31 (IO19), U9.3 (MISO)
/MCU/VSPI_MOSI: U8.37 (IO23), U9.2 (MOSI)
/MCU/VSPI_SCK: U8.30 (IO18), U9.4 (SCK)
/Slaves/LTC6811_1/BAT+: D6.1 (K), D7.1 (K), D8.1 (K), FB1.1, R40.1, R41.1
/Slaves/LTC6811_1/C1: F12.1, J11.1 (Pin_2)
/Slaves/LTC6811_1/C1_G: F13.1, J11.0 (Pin_1)
/Slaves/LTC6811_1/C2: F11.1, J11.2 (Pin_3)
/Slaves/LTC6811_1/C3: F10.1, J11.3 (Pin_4)
/Slaves/LTC6811_1/C4: F9.1, J11.4 (Pin_5)
/Slaves/LTC6811_1/C5: F8.1, J11.5 (Pin_6)
/Slaves/LTC6811_1/C6: F7.1, J10.0 (Pin_1), J11.6 (Pin_7)
/Slaves/LTC6811_1/C7: F6.1, J10.1 (Pin_2)
/Slaves/LTC6811_1/C8: F5.1, J10.2 (Pin_3)
/Slaves/LTC6811_1/C9: F4.1, J10.3 (Pin_4)
/Slaves/LTC6811_1/C10: F3.1, J10.4 (Pin_5)
/Slaves/LTC6811_1/C11: F2.1, J10.5 (Pin_6)
/Slaves/LTC6811_1/C12: F1.1, J10.6 (Pin_7)
/Slaves/LTC6811_1/DRIVE: Q1.1 (B), U11.38 (DRIVE)
/Slaves/LTC6811_1/IMA: R32.1, TR1.3, U11.41 (IMA)
/Slaves/LTC6811_1/IMB: R2.1, TR3.4, U11.47 (IMB)
/Slaves/LTC6811_1/IPA: R29.2, TR1.1, U11.42 (IPA)
/Slaves/LTC6811_1/IPB: R1.2, TR3.6, U11.48 (IPB)
/Slaves/LTC6811_1/T1: C1.1, R3.2, TH1.1, U11.27 (GPIO1)
/Slaves/LTC6811_1/T2: C2.1, R4.1, TH2.1, U11.28 (GPIO2)
/Slaves/LTC6811_1/T3: C3.1, R5.1, TH3.1, U11.29 (GPIO3)
/Slaves/LTC6811_1/T4: C4.1, R6.1, TH4.1, U11.32 (GPIO4)
/Slaves/LTC6811_1/T5: C5.1, R7.1, TH5.1, U11.33 (GPIO5)
/Slaves/LTC6811_1/Vref2: C38.1, R3.1, R4.2, R5.2, R6.2, R7.2, TP4.1, U11.34 (Vref2)
/Slaves/LTC6811_1/Vreg: C40.1, D9.2 (A), Q1.3 (E), R43.2, R44.2, TP3.1, U11.37 (Vreg)
/Slaves/LTC6811_1/cell1/C: C62.1, D20.2 (A), D21.1 (K), R89.1, U11.24 (C1)
/Slaves/LTC6811_1/cell1/C+: F12.2, Q13.2 (S), R85.1, R89.2
/Slaves/LTC6811_1/cell1/S: R90.1, U11.25 (S1)
/Slaves/LTC6811_1/cell2/C: C61.1, D19.2 (A), D20.1 (K), R86.1, U11.22 (C2)
/Slaves/LTC6811_1/cell2/C+: F11.2, Q12.2 (S), R82.1, R86.2
/Slaves/LTC6811_1/cell2/S: R87.1, U11.23 (S2)
/Slaves/LTC6811_1/cell3/C: C60.1, D18.2 (A), D19.1 (K), R83.1, U11.20 (C3)
/Slaves/LTC6811_1/cell3/C+: F10.2, Q11.2 (S), R79.1, R83.2
/Slaves/LTC6811_1/cell3/S: R84.1, U11.21 (S3)
/Slaves/LTC6811_1/cell4/C: C59.1, D17.2 (A), D18.1 (K), R80.1, U11.18 (C4)
/Slaves/LTC6811_1/cell4/C+: F9.2, Q10.2 (S), R76.1, R80.2
/Slaves/LTC6811_1/cell4/S: R81.1, U11.19 (S4)
/Slaves/LTC6811_1/cell5/C: C58.1, D16.2 (A), D17.1 (K), R77.1, U11.16 (C5)
/Slaves/LTC6811_1/cell5/C+: F8.2, Q9.2 (S), R73.1, R77.2
/Slaves/LTC6811_1/cell5/S: R78.1, U11.17 (S5)
/Slaves/LTC6811_1/cell6/C: C57.1, D15.2 (A), D16.1 (K), R74.1, U11.14 (C6)
/Slaves/LTC6811_1/cell6/C+: F7.2, Q8.2 (S), R70.1, R74.2
/Slaves/LTC6811_1/cell6/S: R75.1, U11.15 (S6)
/Slaves/LTC6811_1/cell7/C: C56.1, D14.2 (A), D15.1 (K), R71.1, U11.12 (C7)
/Slaves/LTC6811_1/cell7/C+: F6.2, Q7.2 (S), R67.1, R71.2
/Slaves/LTC6811_1/cell7/S: R72.1, U11.13 (S7)
/Slaves/LTC6811_1/cell8/C: C55.1, D13.2 (A), D14.1 (K), R68.1, U11.10 (C8)
/Slaves/LTC6811_1/cell8/C+: F5.2, Q6.2 (S), R64.1, R68.2
/Slaves/LTC6811_1/cell8/S: R69.1, U11.11 (S8)
/Slaves/LTC6811_1/cell9/S: R66.1, U11.9 (S9)
/Slaves/LTC6811_1/cell10/C: C53.1, D11.2 (A), D12.1 (K), R62.1, U11.6 (C10)
/Slaves/LTC6811_1/cell10/C+: F3.2, Q4.2 (S), R58.1, R62.2
/Slaves/LTC6811_1/cell10/C-: F4.2, Q5.2 (S), R61.1, R65.2
/Slaves/LTC6811_1/cell10/CM: C54.1, D12.2 (A), D13.1 (K), R65.1, U11.8 (C9)
/Slaves/LTC6811_1/cell10/S: R63.1, U11.7 (S10)
/Slaves/LTC6811_1/cell11/C: C52.1, D10.2 (A), D11.1 (K), R59.1, U11.4 (C11)
/Slaves/LTC6811_1/cell11/C+: F2.2, Q3.2 (S), R55.1, R59.2
/Slaves/LTC6811_1/cell11/S: R60.1, U11.5 (S11)
/Slaves/LTC6811_1/cell12/C: C51.1, D10.1 (K), R56.1, U11.2 (C12)
/Slaves/LTC6811_1/cell12/C+: F1.2, FB1.2, Q2.2 (S), R56.2
/Slaves/LTC6811_1/cell12/S: R57.1, U11.3 (S12)
/Slaves/LTC6811_2/BAT+: D22.1 (K), D23.1 (K), D24.1 (K), FB2.1, R91.1, R92.1
/Slaves/LTC6811_2/C1: F25.1, J13.1 (Pin_2)
/Slaves/LTC6811_2/C1_G: F26.1, J13.0 (Pin_1)
/Slaves/LTC6811_2/C2: F24.1, J13.2 (Pin_3)
/Slaves/LTC6811_2/C3: F23.1, J13.3 (Pin_4)
/Slaves/LTC6811_2/C4: F22.1, J13.4 (Pin_5)
/Slaves/LTC6811_2/C5: F21.1, J13.5 (Pin_6)
/Slaves/LTC6811_2/C6: F20.1, J12.0 (Pin_1), J13.6 (Pin_7)
/Slaves/LTC6811_2/C7: F19.1, J12.1 (Pin_2)
/Slaves/LTC6811_2/C8: F18.1, J12.2 (Pin_3)
/Slaves/LTC6811_2/C9: F17.1, J12.3 (Pin_4)
/Slaves/LTC6811_2/C10: F16.1, J12.4 (Pin_5)
/Slaves/LTC6811_2/C11: F15.1, J12.5 (Pin_6)
/Slaves/LTC6811_2/C12: F14.1, J12.6 (Pin_7)
/Slaves/LTC6811_2/DRIVE: Q14.1 (B), U12.38 (DRIVE)
/Slaves/LTC6811_2/IMA: R49.1, TR3.3, U12.41 (IMA)
/Slaves/LTC6811_2/IMB: R155.1, TR7.6, U12.47 (IMB)
/Slaves/LTC6811_2/IPA: R46.2, TR3.1, U12.42 (IPA)
/Slaves/LTC6811_2/IPB: R154.2, TR7.4, U12.48 (IPB)
/Slaves/LTC6811_2/T1: C6.1, R8.2, TH6.1, U12.27 (GPIO1)
/Slaves/LTC6811_2/T2: C7.1, R9.1, TH7.1, U12.28 (GPIO2)
/Slaves/LTC6811_2/T3: C8.1, R10.1, TH8.1, U12.29 (GPIO3)
/Slaves/LTC6811_2/T4: C9.1, R11.1, TH9.1, U12.32 (GPIO4)
/Slaves/LTC6811_2/T5: C10.1, R12.1, TH10.1, U12.33 (GPIO5)
/Slaves/LTC6811_2/Vref2: C64.1, R8.1, R9.2, R10.2, R11.2, R12.2, TP6.1, U12.34 (Vref2)
/Slaves/LTC6811_2/Vreg: C42.1, D25.2 (A), Q14.3 (E), R94.2, R95.2, TP5.1, U12.37 (Vreg)
/Slaves/LTC6811_2/cell1/C: C88.1, D36.2 (A), D37.1 (K), R140.1, U12.24 (C1)
/Slaves/LTC6811_2/cell1/C+: F25.2, Q26.2 (S), R136.1, R140.2
/Slaves/LTC6811_2/cell1/S: R141.1, U12.25 (S1)
/Slaves/LTC6811_2/cell2/C: C87.1, D35.2 (A), D36.1 (K), R137.1, U12.22 (C2)
/Slaves/LTC6811_2/cell2/C+: F24.2, Q25.2 (S), R133.1, R137.2
/Slaves/LTC6811_2/cell2/S: R138.1, U12.23 (S2)
/Slaves/LTC6811_2/cell3/C: C86.1, D34.2 (A), D35.1 (K), R134.1, U12.20 (C3)
/Slaves/LTC6811_2/cell3/C+: F23.2, Q24.2 (S), R130.1, R134.2
/Slaves/LTC6811_2/cell3/S: R135.1, U12.21 (S3)
/Slaves/LTC6811_2/cell4/C: C85.1, D33.2 (A), D34.1 (K), R131.1, U12.18 (C4)
/Slaves/LTC6811_2/cell4/C+: F22.2, Q23.2 (S), R127.1, R131.2
/Slaves/LTC6811_2/cell4/S: R132.1, U12.19 (S4)
/Slaves/LTC6811_2/cell5/C: C84.1, D32.2 (A), D33.1 (K), R128.1, U12.16 (C5)
/Slaves/LTC6811_2/cell5/C+: F21.2, Q22.2 (S), R124.1, R128.2
/Slaves/LTC6811_2/cell5/S: R129.1, U12.17 (S5)
/Slaves/LTC6811_2/cell6/C: C83.1, D31.2 (A), D32.1 (K), R125.1, U12.14 (C6)
/Slaves/LTC6811_2/cell6/C+: F20.2, Q21.2 (S), R121.1, R125.2
/Slaves/LTC6811_2/cell6/S: R126.1, U12.15 (S6)
/Slaves/LTC6811_2/cell7/C: C82.1, D30.2 (A), D31.1 (K), R122.1, U12.12 (C7)
/Slaves/LTC6811_2/cell7/C+: F19.2, Q20.2 (S), R118.1, R122.2
/Slaves/LTC6811_2/cell7/S: R123.1, U12.13 (S7)
/Slaves/LTC6811_2/cell8/C: C81.1, D29.2 (A), D30.1 (K), R119.1, U12.10 (C8)
/Slaves/LTC6811_2/cell8/C+: F18.2, Q19.2 (S), R115.1, R119.2
/Slaves/LTC6811_2/cell8/S: R120.1, U12.11 (S8)
/Slaves/LTC6811_2/cell9/S: R117.1, U12.9 (S9)
/Slaves/LTC6811_2/cell10/C: C79.1, D27.2 (A), D28.1 (K), R113.1, U12.6 (C10)
/Slaves/LTC6811_2/cell10/C+: F16.2, Q17.2 (S), R109.1, R113.2
/Slaves/LTC6811_2/cell10/C-: F17.2, Q18.2 (S), R112.1, R116.2
/Slaves/LTC6811_2/cell10/CM: C80.1, D28.2 (A), D29.1 (K), R116.1, U12.8 (C9)
/Slaves/LTC6811_2/cell10/S: R114.1, U12.7 (S10)
/Slaves/LTC6811_2/cell11/C: C78.1, D26.2 (A), D27.1 (K), R110.1, U12.4 (C11)
/Slaves/LTC6811_2/cell11/C+: F15.2, Q16.2 (S), R106.1, R110.2
/Slaves/LTC6811_2/cell11/S: R111.1, U12.5 (S11)
/Slaves/LTC6811_2/cell12/C: C77.1, D26.1 (K), R107.1, U12.2 (C12)
/Slaves/LTC6811_2/cell12/C+: F14.2, FB2.2, Q15.2 (S), R107.2
/Slaves/LTC6811_2/cell12/S: R108.1, U12.3 (S12)
/Slaves/MB: J6.2, TR7.1
/Slaves/PB: J6.1, TR7.3
GND: C20.2, C21.2, C27.1, C28.1, C29.1, C30.1, C31.1, C32.2, C33.2, C34.1, C35.1, C47.2, C48.2, C49.2, C68.1, D1.1 (K), D4.1 (K), J1.2, J1.4, J1.6, J5.2, J23.2, JP1.3 (B), JP2.3 (B), JP3.3 (B), R35.1, R102.1, R103.1, R104.1, R105.1, R144.1, R148.1, R149.1, R151.1, U1.10 (VSS), U2.2 (VSS), U2.8 (STBY), U3.2 (GND), U4.2 (GND), U5.2, U5.3, U6.2, U6.3, U7.2, U7.3, U8.14 (GND), U8.32 (GND), U8.38 (GND), U9.13 (SLOW), U9.14 (GND)
GND_PACK: C1.2, C2.2, C3.2, C4.2, C5.2, C6.2, C7.2, C8.2, C9.2, C10.2, C24.2, C26.2, C37.2, C38.2, C39.2, C40.2, C41.2, C42.2, C45.2, C50.2, C51.2, C52.2, C53.2, C54.2, C55.2, C56.2, C57.2, C58.2, C59.2, C60.2, C61.2, C62.2, C63.2, C64.2, C65.2, C67.2, C69.2, C70.2, C73.1, C74.2, C77.2, C78.2, C79.2, C80.2, C81.2, C82.2, C83.2, C84.2, C85.2, C86.2, C87.2, C88.2, D6.2 (A), D7.2 (A), D8.2 (A), D21.2 (A), D22.2 (A), D23.2 (A), D24.2 (A), D37.2 (A), F13.2, F26.2, R45.2, R48.2, R88.1, R96.2, R97.2, R98.2, R99.2, R139.1, TH1.2, TH2.2, TH3.2, TH4.2, TH5.2, TH6.2, TH7.2, TH8.2, TH9.2, TH10.2, U11.26 (C0), U11.30 (V-**), U11.31 (V-), U12.26 (C0), U12.30 (V-**), U12.31 (V-)
unnamed: C24.1, R1.1, R2.2
unnamed: C26.1, TR3.5
unnamed: C29.2, TR1.5
unnamed: C30.2, R36.1, R37.2
unnamed: C41.1, Q1.2 (C), Q1.4 (C), R40.2
unnamed: C45.1, TR3.2
unnamed: C50.1, R29.1, R32.2
unnamed: C67.1, Q14.2 (C), Q14.4 (C), R91.2
unnamed: C69.1, TR1.2
unnamed: C70.1, R46.1, R49.2
unnamed: C73.2, R154.1, R155.2
unnamed: C74.1, TR7.5
unnamed: CR1.1, U5.1
unnamed: CR2.1, U6.1
unnamed: CR3.1, U7.1
unnamed: D1.2 (A), R27.1
unnamed: D4.2 (A), R33.1
unnamed: D9.1 (K), R48.1
unnamed: D25.1 (K), R99.1
unnamed: JP1.2 (C), U1.17 (A2)
unnamed: JP2.2 (C), U1.16 (A1)
unnamed: JP3.2 (C), U1.15 (A0)
unnamed: JP4.2 (B), R153.2
unnamed: Q2.3 (D), R55.2
unnamed: Q2.1 (G), R57.2
unnamed: Q3.3 (D), R58.2
unnamed: Q3.1 (G), R60.2
unnamed: Q4.3 (D), R61.2
unnamed: Q4.1 (G), R63.2
unnamed: Q5.3 (D), R64.2
unnamed: Q5.1 (G), R66.2
unnamed: Q6.3 (D), R67.2
unnamed: Q6.1 (G), R69.2
unnamed: Q7.3 (D), R70.2
unnamed: Q7.1 (G), R72.2
unnamed: Q8.3 (D), R73.2
unnamed: Q8.1 (G), R75.2
unnamed: Q9.3 (D), R76.2
unnamed: Q9.1 (G), R78.2
unnamed: Q10.3 (D), R79.2
unnamed: Q10.1 (G), R81.2
unnamed: Q11.3 (D), R82.2
unnamed: Q11.1 (G), R84.2
unnamed: Q12.3 (D), R85.2
unnamed: Q12.1 (G), R87.2
unnamed: Q13.3 (D), R88.2
unnamed: Q13.1 (G), R90.2
unnamed: Q15.3 (D), R106.2
unnamed: Q15.1 (G), R108.2
unnamed: Q16.3 (D), R109.2
unnamed: Q16.1 (G), R111.2
unnamed: Q17.3 (D), R112.2
unnamed: Q17.1 (G), R114.2
unnamed: Q18.3 (D), R115.2
unnamed: Q18.1 (G), R117.2
unnamed: Q19.3 (D), R118.2
unnamed: Q19.1 (G), R120.2
unnamed: Q20.3 (D), R121.2
unnamed: Q20.1 (G), R123.2
unnamed: Q21.3 (D), R124.2
unnamed: Q21.1 (G), R126.2
unnamed: Q22.3 (D), R127.2
unnamed: Q22.1 (G), R129.2
unnamed: Q23.3 (D), R130.2
unnamed: Q23.1 (G), R132.2
unnamed: Q24.3 (D), R133.2
unnamed: Q24.1 (G), R135.2
unnamed: Q25.3 (D), R136.2
unnamed: Q25.1 (G), R138.2
unnamed: Q26.3 (D), R139.2
unnamed: Q26.1 (G), R141.2
unnamed: Q27.1 (G), R13.1, R21.2
unnamed: Q28.1 (G), R14.1, R15.2
unnamed: Q29.1 (G), R16.1, R17.2
unnamed: R15.1, U6.4
unnamed: R17.1, U7.4
unnamed: R21.1, U5.4
unnamed: R102.2, SW1.16, U1.21 (GPA0)
unnamed: R103.2, SW1.15, U1.22 (GPA1)
unnamed: R104.2, SW1.14, U1.23 (GPA2)
unnamed: R105.2, SW1.13, U1.24 (GPA3)
unnamed: R144.2, SW1.12, U1.25 (GPA4)
unnamed: R148.2, SW1.11, U1.26 (GPA5)
unnamed: R149.2, SW1.10, U1.27 (GPA6)
unnamed: R151.2, SW1.9, U1.28 (GPA7)
unnamed: R38.2, U9.16 (IBIAS)
unnamed: R35.2, R38.1, U9.15 (ICMP)
unnamed: R45.1, U11.36 (DTEN)
unnamed: R42.1, U11.45 (IBIAS)
unnamed: R42.2, R97.1, U11.46 (ICMP)
unnamed: R43.1, U11.40 (ISOMD)
unnamed: C37.1, R41.2, U11.1 (V+)
unnamed: C39.1, U11.35 (Vref1)
unnamed: R44.1, U11.39 (WDT)
unnamed: R96.1, U12.36 (DTEN)
unnamed: R47.1, U12.45 (IBIAS)
unnamed: R47.2, R98.1, U12.46 (ICMP)
unnamed: R94.1, U12.40 (ISOMD)
unnamed: C63.1, R92.2, U12.1 (V+)
unnamed: C65.1, U12.35 (Vref1)
unnamed: R95.1, U12.39 (WDT)
